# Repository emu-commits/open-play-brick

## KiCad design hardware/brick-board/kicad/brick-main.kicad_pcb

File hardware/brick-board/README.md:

# Brick board (rev C)

A custom circuit board pair and a printed case for Open Play Brick. This is step 3 of the [roadmap](../../docs/ROADMAP.md): a board a board house can make and assemble from these files.

**Status: a first draft. Nothing here has been built, ordered, or reviewed by anyone with RF board-layout experience.** The roadmap's advice still holds: test a small NFC antenna on the bench (step 2) before paying for these boards.

## Size: 2 x 6, not 2 x 4

Rev C is the roadmap's fallback size: a **2 x 6 brick, six plates (19.2 mm) tall**. It uses the ready-made ESP32-C6-MINI-1 module with its built-in antenna, so there is no bare-chip 2.4 GHz design to verify. The module is 13.2 x 16.6 mm. It fits across the cavity (13.8 mm inside), but with the clear area its antenna needs beyond its end, it takes most of a 2 x 4 brick's length. The extra two studs give room for the rest of the circuit, the battery and the speaker.

A 2 x 4 version would need the bare chip and a chip antenna. That is a separate design.

## What is in it

Two boards, stacked and joined by a 1.27 mm 2 x 5 board-to-board header: a 6-layer main board and a 4-layer face board, both 0.8 mm thick.

| Board | Size | Contents |
|---|---|---|
| main (6 layers) | 45.4 x 13.4 mm | ESP32-C6-MINI-1 (underside), USB-C with ESD protection, LiPo charger (TP4054, 50 mA), battery/USB power path, 3.3 V regulator (RT9080, 2 µA quiescent), battery voltage divider, NFC reader (PN5180) with its 27.12 MHz crystal, amplifier (MAX98357A), accelerometer (LIS2DH12), pixel supply switch and data level shifter, battery and speaker sockets |
| face (4 layers) | 24.4 x 13.4 mm | Printed 6-turn NFC loop with its matching network, eight WS2812B-2020 pixels, colour sensor (TCS34725) and its white lamp |

The face board sits on top so the NFC loop is as close as possible to the tag on top of the brick. Its pixels and colour sensor sit inside the loop. For that reason the face board has **no copper pours**: a solid area of copper inside the loop would act as a shorted turn and weaken the field. Its inner layers carry only a few tracks.

The GPIO numbers match the rev B module build, so the same firmware image runs on both. `gen_board.py` fails if they drift from `firmware/core/pins.h`.

### Cut from rev B to fit

A 2 x 6 brick's main board was about 79% covered by parts and the clearances round them, too dense to route. Three things went to make room:

- **No microphone.** The clap detector hears silence and never fires. GPIO4, its data line, now reads the battery instead.
- **No fuel gauge.** A 1 MΩ / 1 MΩ divider (about 2 µA) feeds the battery voltage to GPIO4 (ADC1 channel 4). The firmware still probes for the MAX17048, finds nothing and carries on. Reading the divider needs a small firmware change that has not been made yet.
- **Smaller sockets.** Battery and speaker both plug into JST-SH 1.0 mm 2-pin sockets (2.9 mm tall). The JST-PH battery socket, with the room its plug needed, took 124 mm² of the top side. The 1.25 mm speaker socket it replaces was 3.53 mm tall, more than the 3.3 mm gap above the speaker.

One part was added: U10, a single-gate buffer (SN74LV1T34) powered from the pixel supply. The pixels run from VSYS, up to about 4.7 V on USB, where a WS2812 needs 0.7 x VDD (about 3.3 V) on its data input. A 3.3 V GPIO is marginal there.

## What to buy besides the boards

No soldering: everything plugs in.

- **Battery:** a 3.7 V single-cell LiPo with a protection circuit, at most 24 mm long, 13 mm wide and 4.5 mm thick (the bay is 24 x 13.8 mm; the module above it leaves 4.9 mm). A "401220" cell (4 x 12 x 20 mm, about 60 to 80 mAh) fits, with a **JST-SH 1.0 mm 2-pin** plug. LiPo plug polarity is not standardised: before plugging in, check that the red wire lands on pin 2, marked `+` on the board.
- **Speaker:** 8 Ω, 0.5 to 1 W, at most 15 x 13 x 4 mm (a "1510" or "1511" size, or 13 mm round), with a **JST-SH 1.0 mm 2-pin** plug.
- The two printed case parts.

## Stack inside the brick

Heights from the bottom of the brick, in mm (from `case/brick_case.scad`):

| From | To | What |
|---|---|---|
| 0.0 | 1.8 | tubes (room for the studs of the brick below) |
| 1.8 | 2.6 | floor (printed base part) |
| 2.6 | 6.6 | speaker at the USB end, battery beside it |
| 7.0 | 9.9 | speaker socket and plug, under the main board above the speaker |
| 9.9 | 10.7 | main board on rails; the ESP32 module hangs below it |
| 10.7 | 16.5 | board-to-board header |
| 16.5 | 17.3 | face board |
| 18.4 | 19.2 | top wall, studs above |

The NFC calculation (`tools/nfc_antenna.py`) assumes 6.6 mm from the loop copper down to the main board's top copper. If the stack changes, change `ground_gap_mm` there too.

## Files

```
tools/design.py        every part, pin and net, with JLCPCB part numbers (the source of truth)
tools/gen_board.py     builds both boards in KiCad: place, route, check
tools/autoplace.py     greedy placer for the small parts
tools/router.py        small maze router (see below)
tools/preroute.py      routes the NFC reader's antenna-side nets first and locks them
tools/stitch_islands.py  a via in each outer ground-pour island that has none
tools/hand_fixes.py    the few hand edits to the routed main board, as code
tools/nfc_antenna.py   loop inductance and PN5180 matching network
tools/gen_sch.py       draws docs/schematic.pdf
tools/gen_fab.py       writes the JLCPCB order files to ../fab/ (refuses a board that fails DRC)
tools/jlc_stock.py     checks every part number against JLCPCB's live stock
tools/kicad.sh         runs any of these in a KiCad 9 container (Docker, no install needed)
tools/kicad-gui.sh     opens a board in KiCad 9's PCB editor from the same container
tools/route_main.sh    routes the main board: preroute, Freerouting 1.9, finish_route.py, stitch_islands.py
tools/render.sh        SVG of a board's layers to ../render/
kicad/                 the generated boards, rules and DRC reports
case/brick_case.scad   printed shell and base
lib/lcsc.pretty/       footprints, from the LCSC/EasyEDA library
```

## Regenerating

Needs KiCad 9 (its Python `pcbnew` module), numpy and scipy, reportlab for the schematic, and Freerouting for the main board. The simplest way is Docker: `tools/kicad.sh` builds a KiCad 9 image with the Python packages (`tools/docker/Dockerfile`) and runs a command in it. For the main board, `tools/route_main.sh` runs Freerouting 1.9 on the host: it needs Java, `xvfb-run` and `freerouting-1.9.0.jar` (default `~/.local/opt/freerouting/freerouting-1.9.0.jar`, or set `FR19_JAR`).

```sh
cd tools
./kicad.sh python3 gen_board.py place     # any command below runs the same way
./route_main.sh                           # main board (see "Routing the main board")
./kicad.sh python3 hand_fixes.py          # the hand edits, after route_main.sh
```

```sh
cd tools
python3 gen_board.py place        # place parts, write ../kicad/*.kicad_pcb (unrouted)
python3 gen_board.py placecheck   # placement DRC: overlaps, clearances
python3 gen_board.py route face   # route the face board with the built-in router
./route_main.sh                   # route the main board (on the host: needs java and xvfb-run)
python3 hand_fixes.py             # the hand edits to the routed main board
python3 gen_board.py check        # full DRC and connectivity
python3 gen_sch.py                # ../docs/schematic.pdf
python3 nfc_antenna.py            # print the antenna and matching design
python3 nfc_antenna.py --check    # check the solver against NXP's worked example
python3 gen_fab.py                # Gerbers, drill, BOM and placement files for JLCPCB
python3 jlc_stock.py              # stock check (plain Python, no KiCad needed)
```

`place` rewrites both boards, so route the face board again after it.

The case, one part at a time:

```sh
openscad -D 'part="shell"' -o shell.stl case/brick_case.scad
openscad -D 'part="base"'  -o base.stl  case/brick_case.scad
```

### Routing the main board

The face board is routed by `tools/router.py`, a small grid maze router (A* on a 0.05 mm grid, with rip-up and retry); it finishes in under a minute. The main board takes more steps. `gen_board.py place` lays some fixed copper first:

- **Module fan-out** (`fanout_module`): each signal pad on the module's two long sides gets a via under the module, between its pads and its centre ground pads, staggered in two columns. The module is 13.2 mm wide on a 13.4 mm board, so those pads can only escape inward, and no autorouter here would place vias under a part by itself. In one straight column, 0.8 mm apart, the vias left 0.35 mm between them, less than any track needs, and walled the NFC reader off from the header on every layer.
- **Reader fan-out** (`fanout_reader`): the PN5180's ground pins get stubs to its exposed pad, its 3V3 and VSYS pins get their own vias, and so does C19's ground pad. Left to the routers, the signal pins either side took that room first.

Then `tools/route_main.sh` does the rest:

1. `preroute.py --analog` routes the reader's antenna-side nets (TX1/TX2, TX1F/TX2F, RXP/RXN and their taps, VMID, VDHF, V1V8, the crystal) with `router.py` on the empty board and locks them.
2. Freerouting **1.9** routes everything else round them (headless, under `xvfb-run`). Freerouting 2.5 oscillated between 55 and 130 open connections on this board; 1.9 converges.
3. `finish_route.py` connects what Freerouting leaves with `router.py`, starting from the copper already there.
4. `stitch_islands.py` puts a via in each piece of the top and bottom ground pours that has none.

Last, `hand_fixes.py` applies three small edits: ground vias for C4/C5, C21 and C1, with one In2 VLED track jogged to make room for C21's, and it removes ground vias the stitching passes stacked on top of each other. Each fix names the copper it changes and refuses to run if that copper is not there, because these edits fit one routing run.

The routing is not reproducible copper for copper: `router.py` and Freerouting do not lay the same tracks twice. Three runs of this recipe (60 and 150 Freerouting passes, and a clean re-run from `place`) each connected every signal net, and each left a different handful of ground joins: pour islands and capacitor ground pads. The committed board is one of those runs, finished by `hand_fixes.py`. After a new run, `gen_board.py check` lists what is left, and `hand_fixes.py` needs new fixes written for it.

`PYTHONHASHSEED` is pinned (0) by `tools/kicad.sh`, because `router.py`'s rip-up order depends on set ordering.

## NFC antenna

`tools/nfc_antenna.py` calculates the loop's inductance from its geometry (about 1.15 µH over the main board), then solves NXP's AN11740 asymmetric matching network for 50 Ω between TX1 and TX2. It checks its own solver against the worked example in that note.

These are first-board values from a calculation. NXP's procedure measures the real coil with a network analyser and then trims the capacitors. The tolerance sweep in the script's output shows how far the real result could land: the drive current stays within the PN5180's limits, and the field stays well above what ISO/IEC 15693 tags need, even in the worst case. Expect to change C1 and C2 on the first boards anyway.

## Routing status

- **Face board (4 layers): routed.** No DRC errors, no missing connections. Its order files are in `fab/brick-face/`.
- **Main board (6 layers): routed.** No DRC errors, no missing connections. Its order files are in `fab/brick-main/`. The DRC warnings left are silkscreen overlaps, footprint-library notices, three tiny dangling track ends, four pads with a single thermal spoke, three silk texts under KiCad's default height, and one fan-out via used on one layer only.

  How it got there: the first draft was about 79% covered and both autorouters left 40 or more connections open. Cutting the microphone and fuel gauge, smaller sockets, 0.2 mm power tracks, 6 layers and a finishing pass brought that down to 13 to 17, almost all of them the NFC reader's own pins. Three changes finished it:

  - The reader's EMC filter coils (L1, L2), VMID capacitor (C19) and receiver taps (R11, R12) are now placed by hand, in the strip between its TX/RX side and the module, each a short stub from its pin. The placer had put them past the module's fan-out vias, so every one of those nets had to cross that wall. Its supply capacitors C12, C13 and C14 are also placed by hand, straight above their pins, and the TX1F/TX2F capacitors sit beside the header pins they feed.
  - The module fan-out vias went under the module and are staggered (see above), and the reader's supply pins got fixed vias.
  - The antenna-side nets are routed first, and the accelerometer (U9) moved to the free top side left of the reader. Under the board, beside the module's pads, it boxed in its own nets.

## Ordering from JLCPCB

`tools/gen_fab.py` writes everything to `fab/<board>/`. It refuses a board that fails DRC or has open connections. Order the two boards as two separate designs, each with assembly:

1. **PCB.** Upload `brick-main-gerbers.zip` (then `brick-face-gerbers.zip` as a second design). Settings: layers as detected (main 6, face 4), **thickness 0.8 mm**, any colour, surface finish ENIG or HASL lead-free. On the 6-layer main board, epoxy-filled and capped vias are JLCPCB's default and free, which suits the vias in the module's and chips' ground pads.
2. **Panelise.** Both boards are smaller than the 70 x 70 mm that JLCPCB's Standard assembly needs, so choose "Panel by JLCPCB" with edge rails. A 2 x 3 or similar panel of the main board, and a 2 x 4 of the face board, gives a handful of each.
3. **Assembly.** Standard PCBA, **both sides**. Upload `-bom.csv` and `-cpl.csv`. On the part-check page every line should match; JP1 (the boot jumper) and ANT1 (the printed loop) are not in the parts list on purpose.
4. **Check the placement preview** part by part, especially U1, U6, U7, U9, U10, the LEDs and J2/J3, and the pin-1 dot of every IC. Bottom-side rotations are the usual source of mistakes. Fix any turned part by adding its footprint to `ROT_FIX` in `gen_fab.py` and regenerating.
5. Run `python3 tools/jlc_stock.py` on the day of the order. When this was written, every part was in stock, but the TCS34725 colour sensor had only 37 left.

Expect 25 or so "extended" parts on each order, each with a small loading fee.

## Assembly

No soldering.

1. Plug the face board's socket onto the main board's header, face board on top, matching the outlines.
2. Plug the speaker into J3 on the underside and the battery into J2 on the top. Before the battery goes in, check its polarity: red to the pin marked `+`.
3. Lay the speaker (facing up) and the battery in their bays on the printed base, battery wires up through the notch in the main board's edge.
4. Push the board stack up into the shell from below, USB-C into its opening, until the main board clicks over its rails. Snap the base in.

The first time, flash the firmware over USB-C from the [build page](https://emu-commits.github.io/open-play-brick/build.html). If the ESP32 does not enter download mode by itself, hold tweezers across JP1 while plugging in the USB cable.

## Not done yet

- **The firmware does not read the battery yet.** It needs to read GPIO4 as an ADC (VBAT = 2 x the reading) instead of the fuel gauge.
- **Nothing has been built.** The NFC antenna in particular is a calculation: expect to change the matching capacitors C40 to C47 on the first boards (`tools/nfc_antenna.py`). The roadmap's bench test of a small antenna (step 2) is still the cheaper first step.
- **Review.** The NFC section (crystal, matching network, loop) and the module's antenna keep-out need review by someone with RF layout experience. The 2.4 GHz antenna sits close to the face board and the battery, so expect less Wi-Fi and Bluetooth range than a bare module.
- **Small battery.** The 2 x 6 bay takes a cell of about 60 to 80 mAh.
- **Fit check of the case** with real boards, battery and speaker.

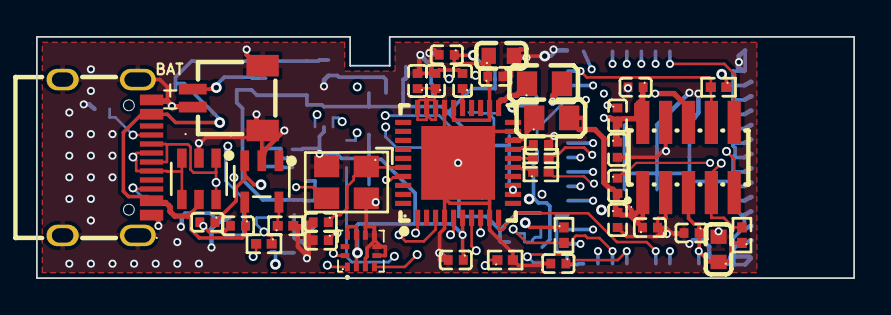
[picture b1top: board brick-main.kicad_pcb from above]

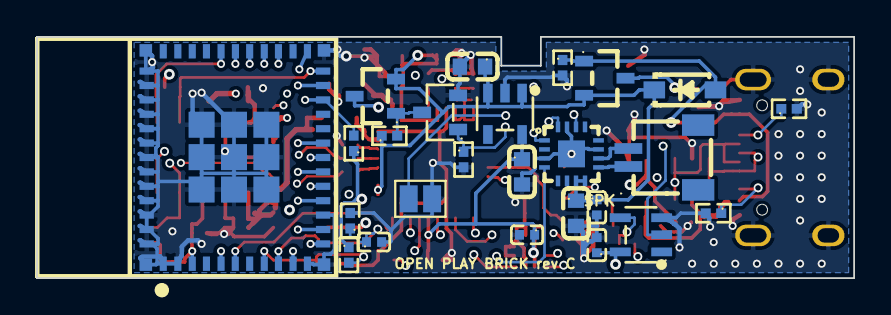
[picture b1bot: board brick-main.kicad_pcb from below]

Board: 6 copper layers, 45.4 x 13.4 mm, 64 parts (25 on the bottom side), 48 nets.

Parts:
C1: 22uF 6.3V; C0603
C2, C13, C15, C17, C18, C19, C27, C29, C30, C31: 100nF; C0402
C3: 1uF; C0402
C4, C5: 4.7uF; C0402
C6, C8, C16, C26: 10uF; C0603
C10, C11: 15pF C0G; C0402
C12, C24, C25: 1nF; C0402
C14: 470nF; C0402
C20, C22: 56pF 1% C0G; C0402
C21, C23: 68pF 1% C0G; C0402
D1: B5819W; SOD-123_L2.7-W1.6-LS3.7-RD-1
J1: USB-C; USB-C_SMD-TYPE-C-31-M-12_1
J2: BATTERY JST-SH 1.0mm; CONN-SMD_2P-P1.00_SM02B-SRSS-TB-LF-SN
J3: SPEAKER JST-SH 1.0mm; CONN-SMD_2P-P1.00_SM02B-SRSS-TB-LF-SN
J4: 2x5 1.27mm male; HDR-SMD_10P-P1.27-V-M-R2-C5-LS5.5_1
JP1: BOOT; SolderJumper-2_P1.3mm_Open_Pad1.0x1.5mm
L1, L2: 470nH MLF2012; L0805
Q1, Q2: AO3401A; SOT-23_L2.9-W1.3-P1.90-LS2.4-BR
Q3: 2N7002; SOT-23-3_L2.9-W1.3-P1.90-LS2.4-BR
R1, R2: 10k; R0402
R4, R5: 5.1k; R0402
R6, R10, R15, R16: 100k; R0402
R7: 20k; R0402
R8, R9: 4.7k; R0402
R11, R12: 3.3k; R0402
R17: 33; R0402
R18, R19: 1M; R0402
U1: ESP32-C6-MINI-1-N4; WIFIM-SMD_61P-L16.6-W13.2-P0.80-ESP32-C6-MINI-1-N4
U2: USBLC6-2SC6; SOT-23-6_L2.9-W1.6-P0.95-LS2.8-BL
U3: TP4054; SOT-23-5_L3.0-W1.7-P0.95-LS2.8-BL
U4: RT9080-33GJ5; TSOT-23-5_L2.9-W1.6-P0.95-LS2.8-BL
U6: PN5180A0HN/C3E; HVQFN-40_L6.0-W6.0-PS0.50-BL
U7: MAX98357AETE+T; TQFN-16_L3.0-W3.0-P0.50-BL-EP1.5
U9: LIS2DH12TR; LGA-12_L2.0-W2.0-P0.50-BL
U10: SN74LV1T34DBVR; SOT-23-5_L3.0-W1.7-P0.95-LS2.8-BL
Y1: 27.12MHz 10pF; CRYSTAL-SMD_4P-L3.2-W2.5-BL-1

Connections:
3V3: C1.1, C2.1, C8.1, C18.1, C29.1, J4.5, R1.1, R2.1, R8.1, R9.1, U1.3, U4.5, U6.6, U9.2, U9.9, U9.10
CC1: J1.A5, R4.1
CC2: J1.B5, R5.1
EN: C3.1, R1.2, U1.8
GND: C1.2, C2.2, C3.2, C4.2, C5.2, C6.2, C8.2, C10.2, C11.2, C12.2, C13.2, C14.2, C15.2, C16.2, C17.2, C18.2, C19.2, C20.2, C21.2, C22.2, C23.2, C26.2, C27.2, C29.2, C30.2, C31.2, J1.1, J1.2, J1.3, J1.4, J1.A1B12, J1.B1A12, J2.1, J2.3, J2.4, J4.3, J4.4, JP1.2, Q3.2, R4.2, R5.2, R6.2, R7.2, R10.2, R16.2, R19.2, U1.1, U1.2, U1.11, U1.14, U1.36, U1.37, U1.38, U1.39, U1.40, U1.41, U1.42, U1.43, U1.44, U1.45, U1.46, U1.47, U1.48, U1.49, U1.50, U1.51, U1.52, U1.53, U2.2, U3.2, U4.2, U6.4, U6.9, U6.19, U6.27, U6.41, U7.3, U7.11, U7.15, U7.17, U9.3, U9.5, U9.6, U9.7, U9.8, U10.3, Y1.2, Y1.4
I2C_SCL: J4.8, R9.2, U1.24, U9.1
I2C_SDA: J4.7, R8.2, U1.25, U9.4
I2S_BCLK: U1.10, U7.16
I2S_DOUT: U1.16, U7.1
I2S_LRCLK: U1.15, U7.14
IMU_INT1: U1.13, U9.12
IO8: R2.2, U1.22
IO9: JP1.1, U1.23
LAMP_EN: J4.10, U1.31
LED_BUF: R17.1, U10.4
LED_DATA: U1.19, U10.2
LED_DIN: J4.9, R17.2
LED_G: Q2.1, Q3.3, R15.2
NFC_BUSY: U1.5, U6.8
NFC_NSS: U1.12, U6.1
NFC_RST: R10.1, U1.6, U6.10
PERIPH_EN: Q3.1, R16.1, U1.30, U7.4
PROG: R7.1, U3.5
RXN: R12.1, U6.15
RXN_C: C25.1, R12.2
RXP: R11.1, U6.16
RXP_C: C24.1, R11.2
SPI_MISO: U1.29, U6.5
SPI_MOSI: U1.28, U6.3
SPI_SCK: U1.27, U6.7
SPK_N: J3.2, U7.10
SPK_P: J3.1, U7.9
TX1: L1.1, U6.21
TX1F: C20.1, C21.1, C24.2, J4.2, L1.2
TX2: L2.1, U6.18
TX2F: C22.1, C23.1, C25.2, J4.1, L2.2
USB_DN: J1.A7, J1.B7, U1.17, U2.1, U2.6
USB_DP: J1.A6, J1.B6, U1.18, U2.3, U2.4
V1V8: C12.1, C13.1, U6.28, U6.29, U6.30
VBAT: C5.1, J2.2, Q1.3, R18.1, U3.3
VBAT_SENSE: C31.1, R18.2, R19.1, U1.9
VBUS: C4.1, D1.2, J1.A4B9, J1.B4A9, Q1.1, R6.1, U2.5, U3.4
VDHF: C14.1, U6.25
VLED: C30.1, J4.6, Q2.3, U10.5
VMID: C19.1, U6.17
VSYS: C6.1, C15.1, C16.1, C17.1, C26.1, C27.1, D1.1, Q1.2, Q2.2, R15.1, U4.1, U4.3, U6.12, U6.13, U6.22, U6.26, U7.7, U7.8
XTAL1: C10.1, U6.36, Y1.1
XTAL2: C11.1, U6.37, Y1.3

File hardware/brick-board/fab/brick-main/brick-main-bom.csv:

Comment,Designator,Footprint,LCSC Part #
22uF 6.3V,C1,C0603,C59461
15pF C0G,"C10,C11",C0402,C1548
1nF,"C12,C24,C25",C0402,C1523
100nF,"C13,C15,C17,C18,C19,C2,C27,C29,C30,C31",C0402,C1525
470nF,C14,C0402,C47339
10uF,"C16,C26,C6,C8",C0603,C19702
56pF 1% C0G,"C20,C22",C0402,C526981
68pF 1% C0G,"C21,C23",C0402,C389103
1uF,C3,C0402,C52923
4.7uF,"C4,C5",C0402,C23733
B5819W,D1,SOD-123_L2.7-W1.6-LS3.7-RD-1,C8598
USB-C,J1,USB-C_SMD-TYPE-C-31-M-12_1,C165948
BATTERY JST-SH 1.0mm,J2,CONN-SMD_2P-P1.00_SM02B-SRSS-TB-LF-SN,C160402
SPEAKER JST-SH 1.0mm,J3,CONN-SMD_2P-P1.00_SM02B-SRSS-TB-LF-SN,C160402
2x5 1.27mm male,J4,HDR-SMD_10P-P1.27-V-M-R2-C5-LS5.5_1,C27985146
470nH MLF2012,"L1,L2",L0805,C92032
AO3401A,"Q1,Q2",SOT-23_L2.9-W1.3-P1.90-LS2.4-BR,C15127
2N7002,Q3,SOT-23-3_L2.9-W1.3-P1.90-LS2.4-BR,C8545
10k,"R1,R2",R0402,C25744
100k,"R10,R15,R16,R6",R0402,C25741
3.3k,"R11,R12",R0402,C25890
33,R17,R0402,C25105
1M,"R18,R19",R0402,C26083
5.1k,"R4,R5",R0402,C25905
20k,R7,R0402,C25765
4.7k,"R8,R9",R0402,C25900
ESP32-C6-MINI-1-N4,U1,WIFIM-SMD_61P-L16.6-W13.2-P0.80-ESP32-C6-MINI-1-N4,C5736265
SN74LV1T34DBVR,U10,SOT-23-5_L3.0-W1.7-P0.95-LS2.8-BL,C100024
USBLC6-2SC6,U2,SOT-23-6_L2.9-W1.6-P0.95-LS2.8-BL,C7519
TP4054,U3,SOT-23-5_L3.0-W1.7-P0.95-LS2.8-BL,C32574
RT9080-33GJ5,U4,TSOT-23-5_L2.9-W1.6-P0.95-LS2.8-BL,C841192
PN5180A0HN/C3E,U6,HVQFN-40_L6.0-W6.0-PS0.50-BL,C1526287
MAX98357AETE+T,U7,TQFN-16_L3.0-W3.0-P0.50-BL-EP1.5,C910544
LIS2DH12TR,U9,LGA-12_L2.0-W2.0-P0.50-BL,C110926
27.12MHz 10pF,Y1,CRYSTAL-SMD_4P-L3.2-W2.5-BL-1,C29975

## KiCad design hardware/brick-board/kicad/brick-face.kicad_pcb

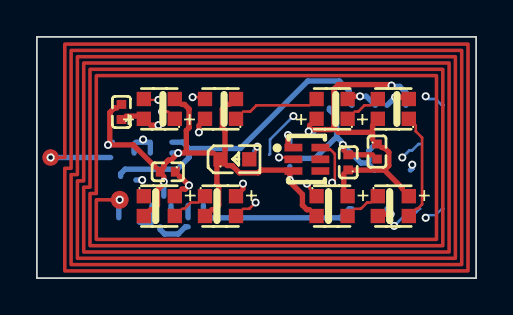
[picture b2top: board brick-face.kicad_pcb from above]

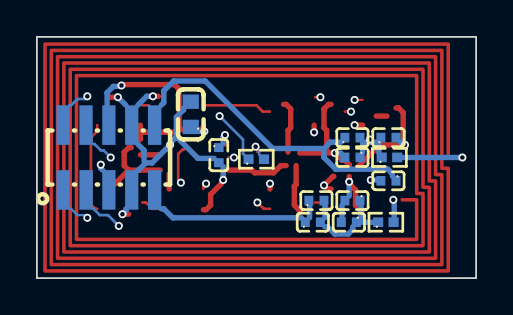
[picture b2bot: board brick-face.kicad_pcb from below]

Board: 4 copper layers, 24.4 x 13.4 mm, 29 parts (14 on the bottom side), 21 nets.

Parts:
ANT1: NFC loop; NFC_LOOP_6T
C40, C44: 47pF 1% C0G; C0402
C41, C45: 4.7pF C0G; C0402
C42, C46: 120pF 1% C0G; C0402
C43, C47: 56pF 1% C0G; C0402
C50, C51, C52, C53, C55: 100nF; C0402
C54: 10uF; C0603
J5: 2x5 1.27mm female; HDR-SMD_10P-P1.27-V-F-R2-C5-LS4.8
LED1, LED2, LED3, LED4, LED5, LED6, LED7, LED8: WS2812B-2020; LED-SMD_4P-L2.2-W2.0-P1.00_WS2815C-2020-4P
LED9: white; LED0603-RD_WHITE
R30, R31: 3.0; R0402
R32: 47; R0402
U20: TCS34725FN; SENSOR-SMD_TCS34725FN

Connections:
3V3: C55.1, J5.5, U20.1
ANT_A: ANT1.1, R30.2
ANT_B: ANT1.2, R31.2
GND: C42.2, C43.2, C46.2, C47.2, C50.2, C51.2, C52.2, C53.2, C54.2, C55.2, J5.7, J5.8, LED1.2, LED2.2, LED3.2, LED4.2, LED5.2, LED6.2, LED7.2, LED8.2, LED9.1, U20.3
I2C_SCL: J5.4, U20.2
I2C_SDA: J5.3, U20.6
LAMP_A: LED9.2, R32.2
LAMP_EN: J5.2, R32.1
LED_DIN: J5.1, LED1.3
MA1: C40.2, C41.2, C42.1, C43.1, R30.1
MB1: C44.2, C45.2, C46.1, C47.1, R31.1
PIX1: LED1.1, LED2.3
PIX2: LED2.1, LED3.3
PIX3: LED3.1, LED4.3
PIX4: LED4.1, LED5.3
PIX5: LED5.1, LED6.3
PIX6: LED6.1, LED7.3
PIX7: LED7.1, LED8.3
TX1F: C40.1, C41.1, J5.10
TX2F: C44.1, C45.1, J5.9
VLED: C50.1, C51.1, C52.1, C53.1, C54.1, J5.6, LED1.4, LED2.4, LED3.4, LED4.4, LED5.4, LED6.4, LED7.4, LED8.4

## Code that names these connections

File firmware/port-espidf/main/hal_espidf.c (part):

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{
    radio_rx_handler = on_radio;

    spi_bus_config_t bus = { .mosi_io_num = PIN_SPI_MOSI, .miso_io_num = PIN_SPI_MISO, .sclk_io_num = PIN_SPI_SCK,
                             .quadwp_io_num = -1, .quadhd_io_num = -1 };
    spi_device_interface_config_t dev = { .clock_speed_hz = 2000000, .mode = 0, .spics_io_num = -1, .queue_size = 1 };
    ESP_ERROR_CHECK(spi_bus_initialize(SPI2_HOST, &bus, SPI_DMA_DISABLED));
    ESP_ERROR_CHECK(spi_bus_add_device(SPI2_HOST, &dev, &spi));

    /* The Feather and the sensor breakouts carry the I2C pull-ups. */
    i2c_master_bus_config_t i2c = { .i2c_port = I2C_NUM_0, .sda_io_num = PIN_I2C_SDA, .scl_io_num = PIN_I2C_SCL,
                                    .clk_source = I2C_CLK_SRC_DEFAULT, .glitch_ignore_cnt = 7 };
    ESP_ERROR_CHECK(i2c_new_master_bus(&i2c, &i2c_bus));

    /* Pixel data: 800 kHz, 0 = 0.3 us high, 1 = 0.6 us high, at 0.1 us per tick. */
    rmt_tx_channel_config_t rmt = { .gpio_num = PIN_LED_DATA, .clk_src = RMT_CLK_SRC_DEFAULT, .resolution_hz = 10000000,
                                    .mem_block_symbols = 64, .trans_queue_depth = 1 };
    ESP_ERROR_CHECK(rmt_new_tx_channel(&rmt, &led_chan));
    rmt_bytes_encoder_config_t enc = {
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    i2s_std_config_t std = {
        .clk_cfg = I2S_STD_CLK_DEFAULT_CONFIG(I2S_RATE),
        .slot_cfg = I2S_STD_PHILIPS_SLOT_DEFAULT_CONFIG(I2S_DATA_BIT_WIDTH_16BIT, I2S_SLOT_MODE_MONO),
        .gpio_cfg = { .mclk = I2S_GPIO_UNUSED, .bclk = PIN_I2S_BCLK, .ws = PIN_I2S_LRCLK, .dout = PIN_I2S_DOUT, .din = PIN_I2S_DIN },
    };
    std.slot_cfg.slot_bit_width = I2S_SLOT_BIT_WIDTH_32BIT;
    /* The default macro sets the word-select pulse to the data width (16
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    /* On chips without per-pin hold in deep sleep, holds need this too. */
    gpio_deep_sleep_hold_en();
#endif
    esp_sleep_enable_ext1_wakeup_io(1ULL << PIN_IMU_INT1, ESP_EXT1_WAKEUP_ANY_HIGH);
    esp_deep_sleep_start();
}

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
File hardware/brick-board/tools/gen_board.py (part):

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    # in the strip between its TX/RX side and the module's fan-out vias, each
    # a short stub from its pin. The placer scattered them past the vias, and
    # neither router could get the pins out (13 to 17 connections open).
    "L1": (28.2, 2.6, 0, "T"),    # TX1 (pin 21, top right corner) -> TX1F; clear of U1.24's fan-out via
    "L2": (28.6, 4.5, 0, "T"),    # TX2 (pin 18) -> TX2F
    "C19": (28.0, 6.0, 0, "T"),   # VMID (pin 17)
    "R11": (28.0, 6.75, 0, "T"),  # RXP (pin 16) -> RXP_C
    "R12": (28.0, 7.5, 0, "T"),   # RXN (pin 15) -> RXN_C
    "C13": (21.15, 2.45, 90, "T"),  # V1V8 (pins 28-30), straight above them: placed by the
    "C12": (22.15, 2.45, 90, "T"),  # placer, the VSYS capacitors took this spot and V1V8 stayed open
    "C14": (23.65, 2.45, 90, "T"),  # VDHF (pin 25), likewise
    "U9": (18.0, 11.9, 0, "T"),   # accelerometer: on the free top side left of the reader; under the
                                  # board beside the module's pads it boxed in its own nets
    "J4": (36.2, 6.7, 0, "T"),    # to the face board
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    ("C16", "U6", "22", T), ("C17", "U6", "22", T), ("C15", "U6", "26", T),
    ("C18", "U6", "6", T),
    ("R10", "U6", "10", T),
    # TX1F/TX2F filter and coupling capacitors beside the header pins they feed
    ("C24", "J4", "2", T), ("C20", "J4", "2", T), ("C21", "J4", "2", T),
    ("C25", "J4", "1", T), ("C22", "J4", "1", T), ("C23", "J4", "1", T), ("C10", "Y1", "1", T), ("C11", "Y1", "3", T),
    # module support
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    """Fixed escapes for the PN5180's supply and ground pins and C19's
    ground, laid before any routing. Left to the routers, the signal pins on
    each side of them took the room first: 3V3 (pin 6, between two SPI
    pins), VSYS (pins 12 and 13) and C19's ground pad stayed open."""
    u6 = b.FindFootprintByReference("U6")
    def pad(ref, num):
        p = b.FindFootprintByReference(ref).FindPadByNumber(num)
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    p, x, y = pad("U6", "6")
    stub(p, [(x, y), (x, y + 0.95)], 0.2)
    add_via(b, {}, None, x, y + 0.95, 0.45, 0.25, net_obj=p.GetNet())
    # VSYS, pins 12 and 13: joined, with a via between them (filled and
    # capped, JLCPCB's default on 6 layers)
    p12, x12, y12 = pad("U6", "12")
    p13, x13, y13 = pad("U6", "13")
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
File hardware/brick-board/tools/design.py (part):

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    mod[p] = "NC_M" + p
net_of_gpio = {v: k for k, v in GPIO.items()}
for g, pad in MODULE_PAD.items():
    mod[pad] = net_of_gpio.get(g, {4: "VBAT_SENSE", 8: "IO8", 9: "IO9", 15: "NC_IO15", 20: "NC_IO20"}.get(g))
part("U1", M, "bottom", "WIFIM-SMD_61P-L16.6-W13.2-P0.80-ESP32-C6-MINI-1-N4", "ESP32-C6-MINI-1-N4", "C5736265", mod)
C("C1", M, "top", "22uF 6.3V", C22U, "3V3", "GND", "module supply", fp="C0603")
C("C2", M, "top", "100nF", C100N, "3V3", "GND", "module supply")
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C("C41", Fb, "bottom", "4.7pF C0G", "C325453", "TX1F", "MA1", "C1 (series)")
C("C42", Fb, "bottom", "120pF 1% C0G", "C541468", "MA1", "GND", "C2 (parallel)")
C("C43", Fb, "bottom", "56pF 1% C0G", "C526981", "MA1", "GND", "C2 (parallel)")
R("R30", Fb, "bottom", "3.0", "C309547", "MA1", "ANT_A", "Rq (damping)")
C("C44", Fb, "bottom", "47pF 1% C0G", "C277503", "TX2F", "MB1", "C1 (series)")
C("C45", Fb, "bottom", "4.7pF C0G", "C325453", "TX2F", "MB1", "C1 (series)")
C("C46", Fb, "bottom", "120pF 1% C0G", "C541468", "MB1", "GND", "C2 (parallel)")
C("C47", Fb, "bottom", "56pF 1% C0G", "C526981", "MB1", "GND", "C2 (parallel)")
R("R31", Fb, "bottom", "3.0", "C309547", "MB1", "ANT_B", "Rq (damping)")

# Eight pixels in a chain, 1..8. WS2812B-2020 pads: 1 DOUT, 2 GND, 3 DIN, 4 VDD.
chain = ["LED_DIN"] + ["PIX%d" % i for i in range(1, 8)] + ["NC_PIX8"]
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C("C55", Fb, "bottom", "100nF", C100N, "3V3", "GND")
part("LED9", Fb, "top", "LED0603-RD_WHITE", "white", "C965808", {1: "GND", 2: "LAMP_A"},
     "lamp for the colour sensor (pad 1 = cathode)")
R("R32", Fb, "bottom", "47", "C25118", "LAMP_EN", "LAMP_A", "lamp, driven straight from GPIO16: about 5 to 10 mA")


def parts(board=None):
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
